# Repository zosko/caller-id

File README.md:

# Caller ID

Caller ID module that can be used in various projects, providing reliable identification of incoming calls along with essential details such as phone numbers, timestamps, and optional contact name resolution. This module ([origin](https://github.com/dilshan/arduino-caller-id)) is designed and modified to be easily integrated into different systems.

## Scheme

Board | Preview 
-----|-----
|

## Package example

```
INCOMING CALL
MDMF PACKET
 MSG HEADER: 1
 MSG LEN: 8
 MSG END 07050400
Jul0504:00
 MSG HEADER: 2
 MSG LEN: 9
 MSG END 055857857
055857857
 MSG HEADER: 7
 MSG LEN: E
 MSG END Bosko Pet
Bosko Pet
MDMF PACKET END
````

## Sponsorship

**This project is proudly sponsored by [PCBWay](https://pcbway.com).**

PCBWay specializes in manufacturing high-quality printed circuit boards (PCBs), making them accessible and affordable for both hobbyists and professionals.

Their range of services includes:

- PCB prototyping
- Assembly services
- Instant order quotations
- Expert verification processes
- A user-friendly, hassle-free ordering system

I'm sincerely grateful to PCBWay for their generous support in making this project possible.

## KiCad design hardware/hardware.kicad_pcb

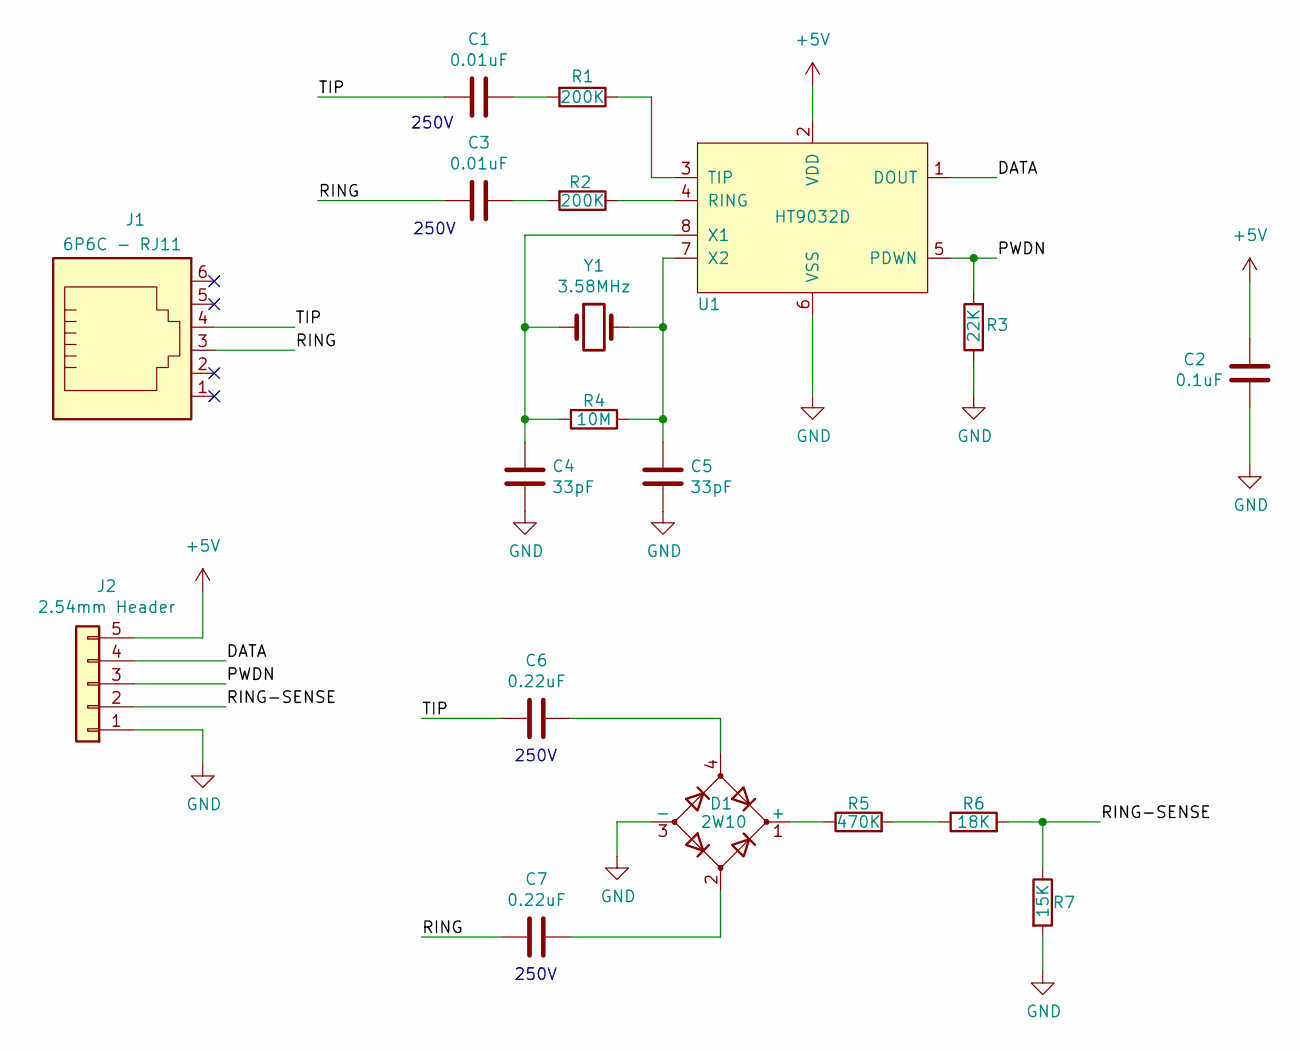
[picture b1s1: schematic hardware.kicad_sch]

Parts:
C1, C3: 0.01uF; C_Disc_D10.5mm_W5.0mm_P5.00mm; MFR.Part MPP103J2G1305085LC; JLCPCB Part C109484
C2: 0.1uF; C_Rect_L9.0mm_W4.2mm_P7.50mm_MKT; MFR.Part CT4-0805B104K500F3; JLCPCB Part C84772
C4, C5: 33pF; C_Disc_D3.8mm_W2.6mm_P2.50mm; MFR.Part CC4-0805N330J500F3; JLCPCB Part C94712
C6, C7: 0.22uF; C_Rect_L11.0mm_W7.3mm_P10.00mm_MKT; MFR.Part CBB21-224J-400V; JLCPCB Part C914540
D1: 2W10; Diode_Bridge_Round_D9.0mm; MFR.Part 2W10G-E4/51; JLCPCB Part C266671
J1: 6P6C - RJ11; RJ25_Wayconn_MJEA-660X1_Horizontal; MFR.Part 520186646; JLCPCB Part C588140
J2: 2.54mm Header; PinHeader_1x05_P2.54mm_Vertical; MFR.Part HX PZ2.54-1x5P ZZ; JLCPCB Part C32713271
R1, R2: 200K; R_Axial_DIN0207_L6.3mm_D2.5mm_P10.16mm_Horizontal; MFR.Part CR1/4W-200K±5%-ST52; JLCPCB Part C2894668
R3: 22K; R_Axial_DIN0207_L6.3mm_D2.5mm_P10.16mm_Horizontal; MFR.Part CR1/4W-22K±5%-ST52; JLCPCB Part C2894673
R4: 10M; R_Axial_DIN0207_L6.3mm_D2.5mm_P10.16mm_Horizontal; MFR.Part CR1/4W-10M±5%-ST52; JLCPCB Part C2894650
R5: 470K; R_Axial_DIN0207_L6.3mm_D2.5mm_P10.16mm_Horizontal; MFR.Part CF1/4W-470KΩ±5% T; JLCPCB Part C120119
R6: 18K; R_Axial_DIN0207_L6.3mm_D2.5mm_P10.16mm_Horizontal; MFR.Part CF1/4W-18KΩ±5% T52; JLCPCB Part C120085
R7: 15K; R_Axial_DIN0207_L6.3mm_D2.5mm_P10.16mm_Horizontal; MFR.Part CR1/4W-15K±5%-OT26; JLCPCB Part C2894540
U1: HT9032D; DIP-8_W7.62mm_LongPads; MFR.Part HT9032D(LX); JLCPCB Part C22397227
Y1: 3.58MHz; Crystal_HC49-U_Vertical; MFR.Part X49SD358MSB2SC-1; JLCPCB Part C20617999

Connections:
+5V: C2.2, J2.5, U1.2 (VDD)
/DATA: J2.4, U1.1 (DOUT)
/PWDN: J2.3, R3.2, U1.5 (PDWN)
/RING: C3.2, C7.2, J1.3
/RING-SENSE: J2.2, R6.2, R7.1
/TIP: C1.2, C6.2, J1.4
GND: C2.1, C4.2, C5.2, D1.3 (-), J2.1, R3.1, R7.2, U1.6 (VSS)
unnamed: C1.1, R1.2
unnamed: C3.1, R2.2
unnamed: C6.1, D1.4
unnamed: C7.1, D1.2
unnamed: D1.1 (+), R5.1
unnamed: R5.2, R6.1
unnamed: R2.1, U1.4 (RING)
unnamed: R1.1, U1.3 (TIP)
unnamed: C4.1, R4.2, U1.8 (X1), Y1.1
unnamed: C5.1, R4.1, U1.7 (X2), Y1.2

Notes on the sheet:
250V

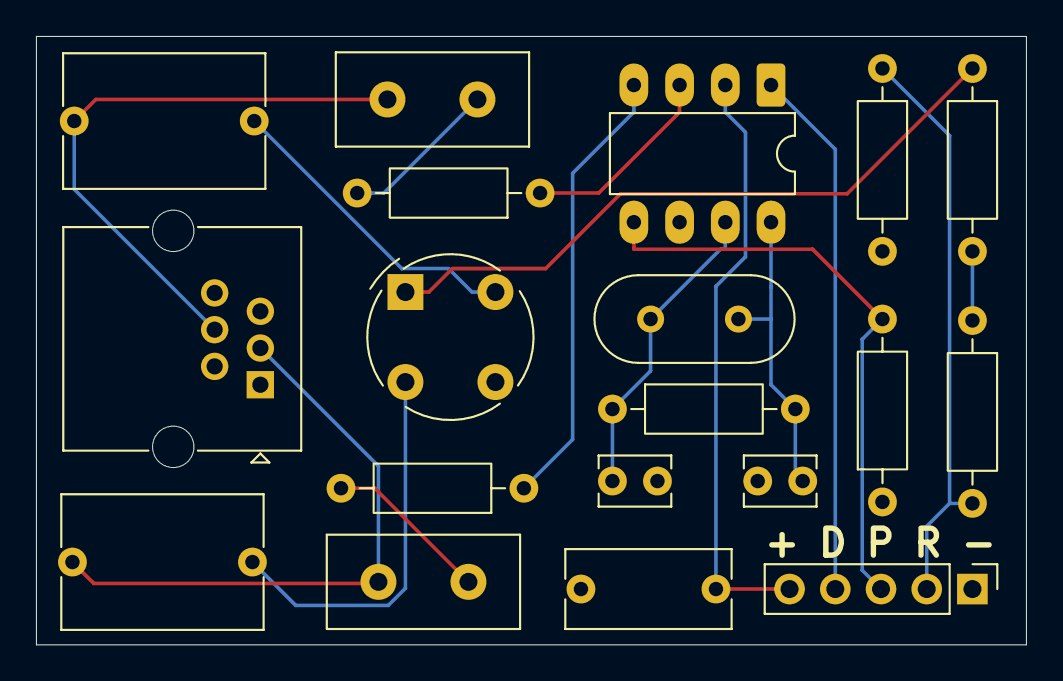
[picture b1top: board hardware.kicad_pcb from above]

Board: 2 copper layers, 55.0 x 33.8 mm, 19 parts (0 on the bottom side), 17 nets.

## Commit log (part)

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2026-04-01 add project
2026-04-01 tidy
2026-06-27 add bom file
